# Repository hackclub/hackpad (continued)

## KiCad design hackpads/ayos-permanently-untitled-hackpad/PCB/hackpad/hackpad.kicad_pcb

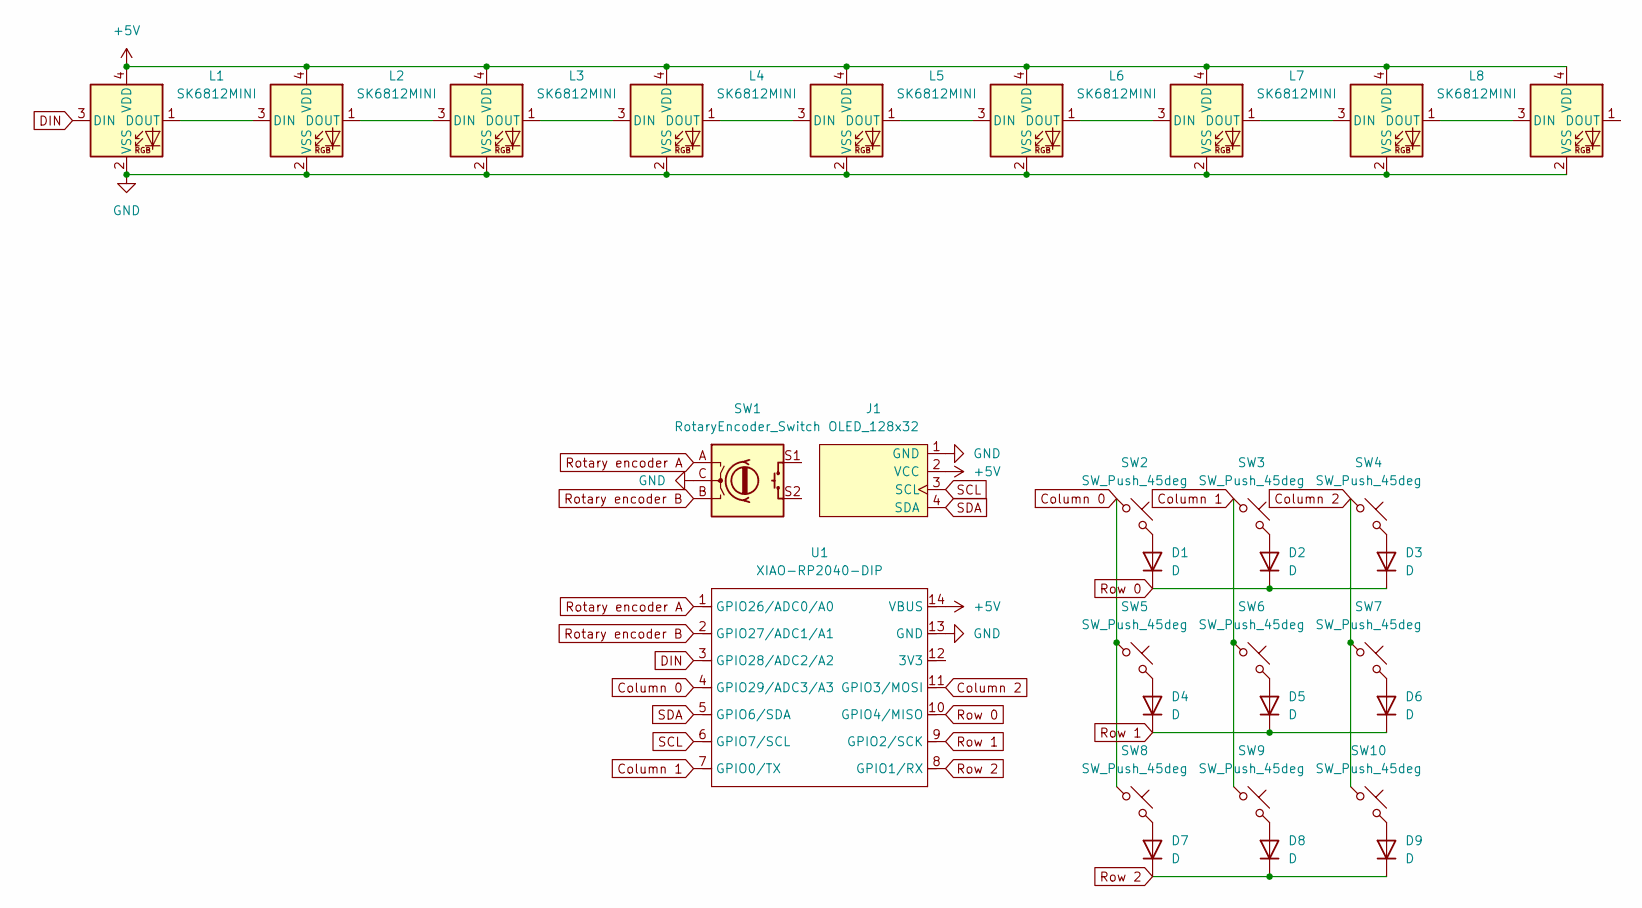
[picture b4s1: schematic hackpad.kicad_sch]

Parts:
D1, D2, D3, D4, D5, D6, D7, D8, D9: D; D_DO-35_SOD27_P7.62mm_Horizontal
J1: OLED_128x32
L1, L2, L3, L4, L5, L6, L7, L8, L9: SK6812MINI; SK6812MINI-E
SW1: RotaryEncoder_Switch; RotaryEncoder_Alps_EC11E-Switch_Vertical_H20mm_CircularMoun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
SW2, SW3, SW4, SW5, SW6, SW7, SW8, SW9, SW10: SW_Push_45deg; SW_Cherry_MX_1.00u_PCB
U1: XIAO-RP2040-DIP

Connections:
+5V: J1.2 (VCC), L1.4 (VDD), L2.4 (VDD), L3.4 (VDD), L4.4 (VDD), L5.4 (VDD), L6.4 (VDD), L7.4 (VDD), L8.4 (VDD), L9.4 (VDD), U1.14 (VBUS)
Column 0: SW2.1, SW5.1, SW8.1, U1.4 (GPIO29/ADC3/A3)
Column 1: SW3.1, SW6.1, SW9.1, U1.7 (GPIO0/TX)
Column 2: SW4.1, SW7.1, SW10.1, U1.11 (GPIO3/MOSI)
DIN: L1.3 (DIN), U1.3 (GPIO28/ADC2/A2)
GND: J1.1 (GND), L1.2 (VSS), L2.2 (VSS), L3.2 (VSS), L4.2 (VSS), L5.2 (VSS), L6.2 (VSS), L7.2 (VSS), L8.2 (VSS), L9.2 (VSS), SW1.C, U1.13 (GND)
unnamed: D1.2 (A), SW2.2
unnamed: D2.2 (A), SW3.2
unnamed: D3.2 (A), SW4.2
unnamed: D4.2 (A), SW5.2
unnamed: D5.2 (A), SW6.2
unnamed: D6.2 (A), SW7.2
unnamed: D7.2 (A), SW8.2
unnamed: D8.2 (A), SW9.2
unnamed: D9.2 (A), SW10.2
unnamed: L1.1 (DOUT), L2.3 (DIN)
unnamed: L2.1 (DOUT), L3.3 (DIN)
unnamed: L3.1 (DOUT), L4.3 (DIN)
unnamed: L4.1 (DOUT), L5.3 (DIN)
unnamed: L5.1 (DOUT), L6.3 (DIN)
unnamed: L6.1 (DOUT), L7.3 (DIN)
unnamed: L7.1 (DOUT), L8.3 (DIN)
unnamed: L8.1 (DOUT), L9.3 (DIN)
Rotary encoder A: SW1.A, U1.1 (GPIO26/ADC0/A0)
Rotary encoder B: SW1.B, U1.2 (GPIO27/ADC1/A1)
Row 0: D1.1 (K), D2.1 (K), D3.1 (K), U1.10 (GPIO4/MISO)
Row 1: D4.1 (K), D5.1 (K), D6.1 (K), U1.9 (GPIO2/SCK)
Row 2: D7.1 (K), D8.1 (K), D9.1 (K), U1.8 (GPIO1/RX)
SCL: J1.3 (SCL), U1.6 (GPIO7/SCL)
SDA: J1.4 (SDA), U1.5 (GPIO6/SDA)

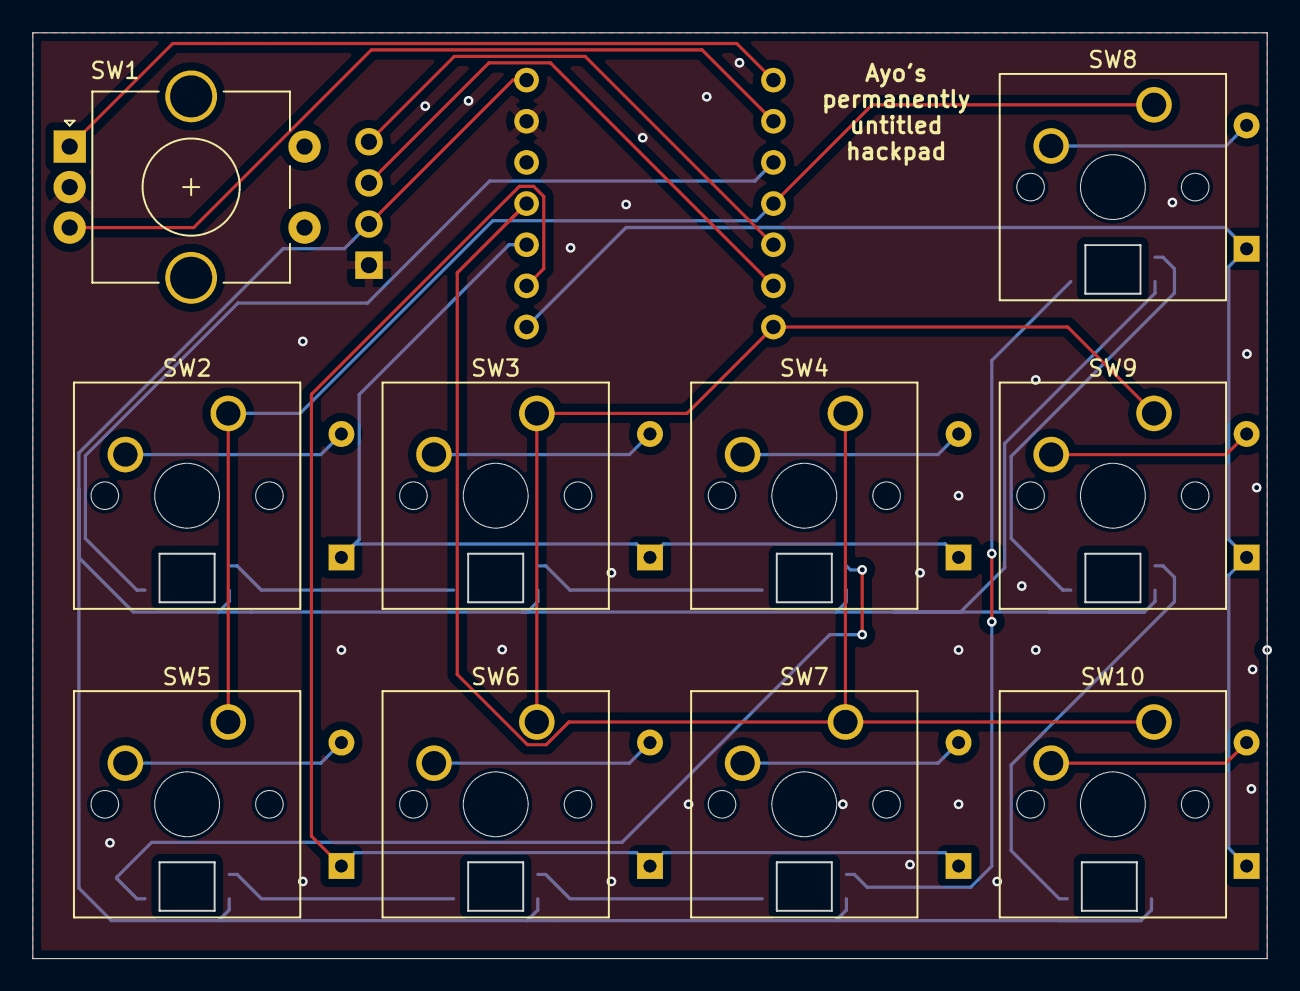
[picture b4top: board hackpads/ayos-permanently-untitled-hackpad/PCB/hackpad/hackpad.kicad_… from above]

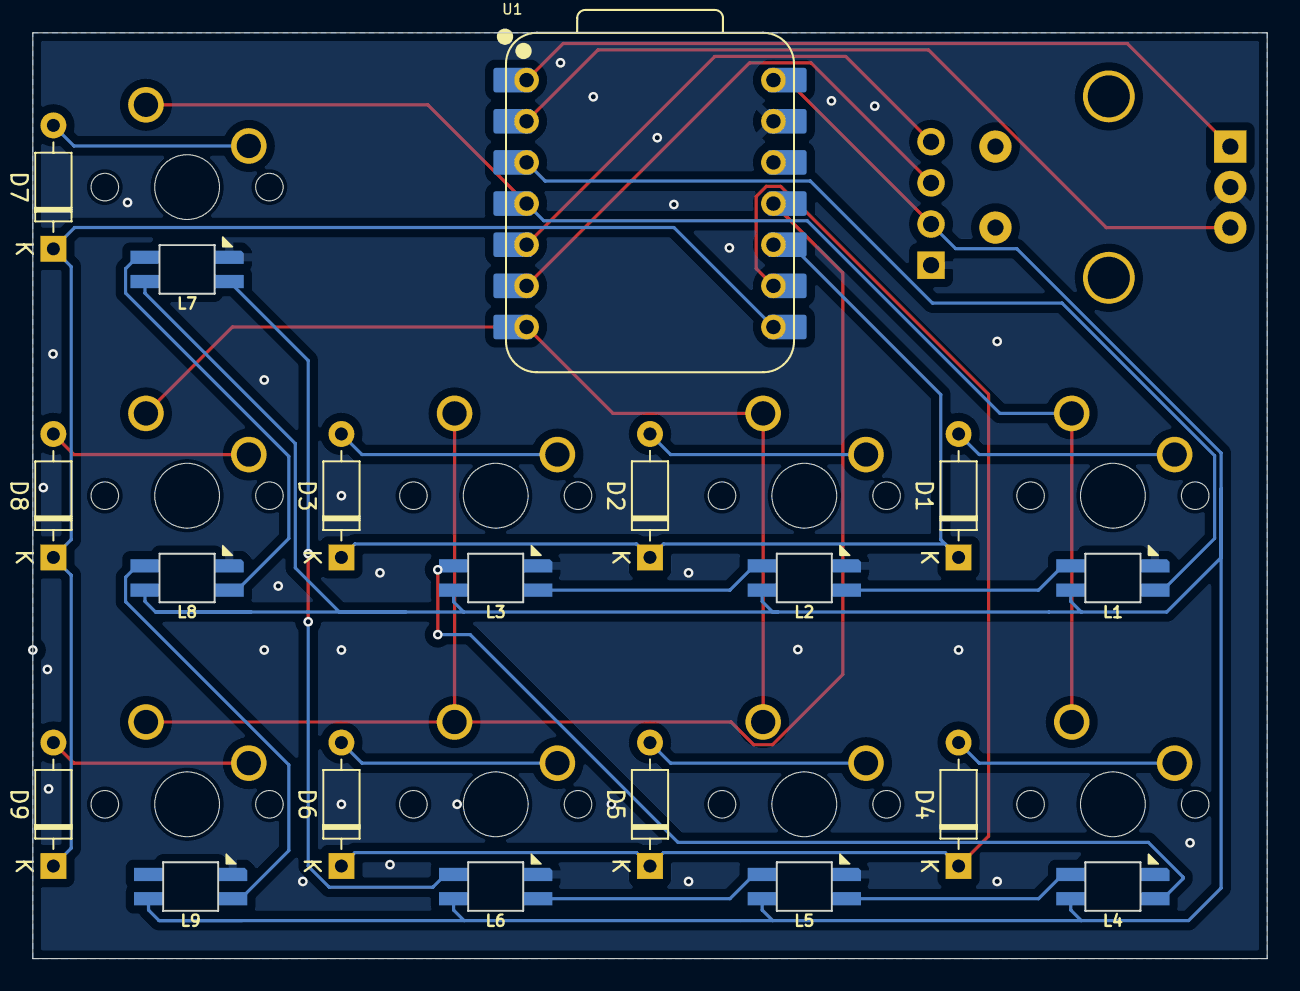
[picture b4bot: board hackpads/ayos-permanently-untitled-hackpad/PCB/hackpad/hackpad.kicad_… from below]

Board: 2 copper layers, 76.2 x 57.1 mm, 30 parts (19 on the bottom side), 30 nets.

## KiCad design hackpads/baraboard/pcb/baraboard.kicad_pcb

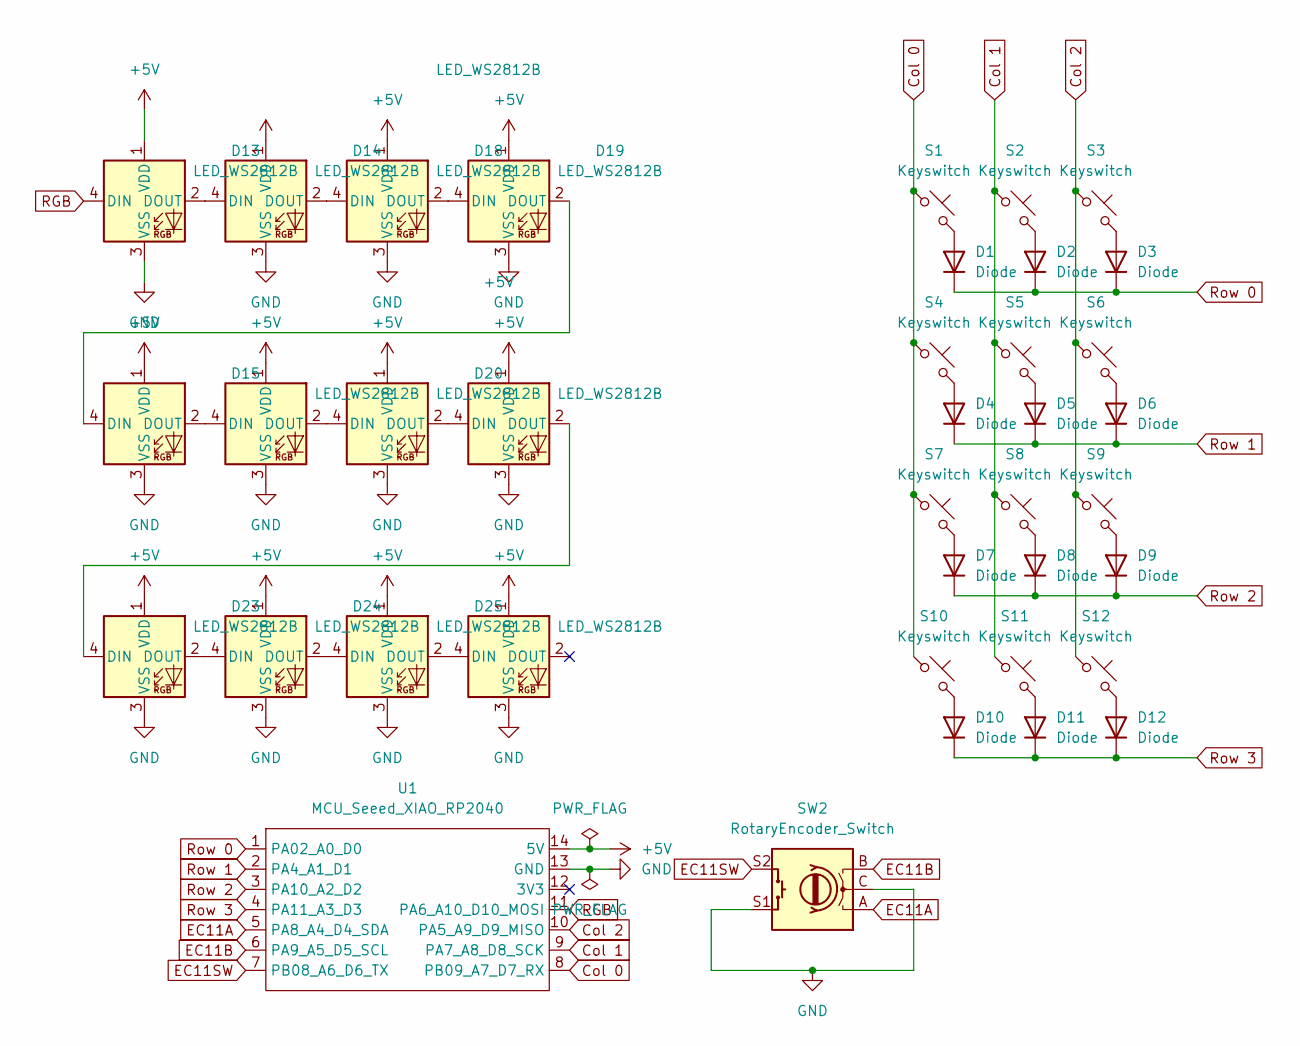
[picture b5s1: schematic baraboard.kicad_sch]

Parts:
D1, D2, D3, D4, D5, D6, D7, D8, D9, D10, D11, D12: Diode; Diode_DO-35
D13, D14, D15, D16, D18, D19, D20, D21, D23, D24, D25, D26: LED_WS2812B; LED_SK6812MINI
S1, S2, S3, S4, S5, S6, S7, S8, S9, S10, S12: Keyswitch; MX_PCB_1.00u
S11: Keyswitch; MX_PCB_2.00u
SW2: RotaryEncoder_Switch; Encoder_EC11_MX
U1: MCU_Seeed_XIAO_RP2040; Seeed_XIAO_RP2040

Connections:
+5V: D13.1 (VDD), D14.1 (VDD), D15.1 (VDD), D16.1 (VDD), D18.1 (VDD), D19.1 (VDD), D20.1 (VDD), D21.1 (VDD), D23.1 (VDD), D24.1 (VDD), D25.1 (VDD), D26.1 (VDD), U1.14 (5V)
Col 0: S1.1, S4.1, S7.1, S10.1, U1.8 (PB09_A7_D7_RX)
Col 1: S2.1, S5.1, S8.1, S11.1, U1.9 (PA7_A8_D8_SCK)
Col 2: S3.1, S6.1, S9.1, S12.1, U1.10 (PA5_A9_D9_MISO)
EC11A: SW2.A, U1.5 (PA8_A4_D4_SDA)
EC11B: SW2.B, U1.6 (PA9_A5_D5_SCL)
EC11SW: SW2.S2, U1.7 (PB08_A6_D6_TX)
GND: D13.3 (VSS), D14.3 (VSS), D15.3 (VSS), D16.3 (VSS), D18.3 (VSS), D19.3 (VSS), D20.3 (VSS), D21.3 (VSS), D23.3 (VSS), D24.3 (VSS), D25.3 (VSS), D26.3 (VSS), SW2.C, SW2.S1, U1.13 (GND)
unnamed: D1.2 (A), S1.2
unnamed: D2.2 (A), S2.2
unnamed: D3.2 (A), S3.2
unnamed: D4.2 (A), S4.2
unnamed: D5.2 (A), S5.2
unnamed: D6.2 (A), S6.2
unnamed: D7.2 (A), S7.2
unnamed: D8.2 (A), S8.2
unnamed: D9.2 (A), S9.2
unnamed: D10.2 (A), S10.2
unnamed: D11.2 (A), S11.2
unnamed: D12.2 (A), S12.2
unnamed: D13.2 (DOUT), D14.4 (DIN)
unnamed: D14.2 (DOUT), D15.4 (DIN)
unnamed: D15.2 (DOUT), D19.4 (DIN)
unnamed: D16.4 (DIN), D18.2 (DOUT)
unnamed: D16.2 (DOUT), D20.4 (DIN)
unnamed: D18.4 (DIN), D19.2 (DOUT)
unnamed: D20.2 (DOUT), D21.4 (DIN)
unnamed: D21.2 (DOUT), D23.4 (DIN)
unnamed: D23.2 (DOUT), D24.4 (DIN)
unnamed: D24.2 (DOUT), D25.4 (DIN)
unnamed: D25.2 (DOUT), D26.4 (DIN)
RGB: D13.4 (DIN), U1.11 (PA6_A10_D10_MOSI)
Row 0: D1.1 (K), D2.1 (K), D3.1 (K), U1.1 (PA02_A0_D0)
Row 1: D4.1 (K), D5.1 (K), D6.1 (K), U1.2 (PA4_A1_D1)
Row 2: D7.1 (K), D8.1 (K), D9.1 (K), U1.3 (PA10_A2_D2)
Row 3: D10.1 (K), D11.1 (K), D12.1 (K), U1.4 (PA11_A3_D3)

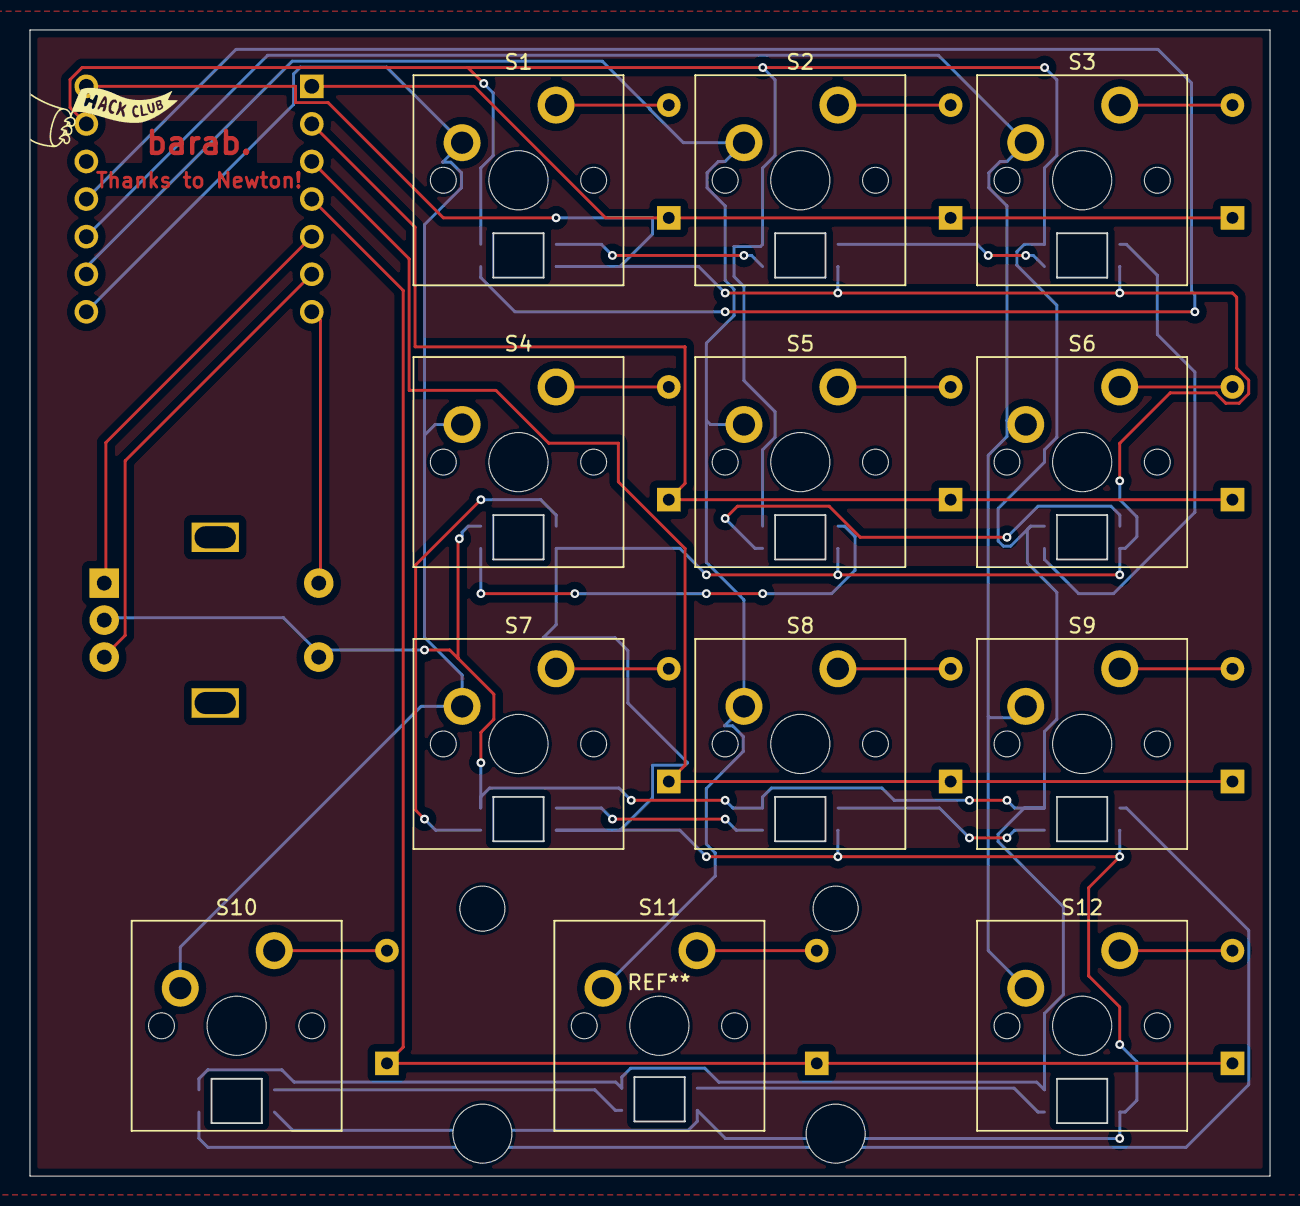
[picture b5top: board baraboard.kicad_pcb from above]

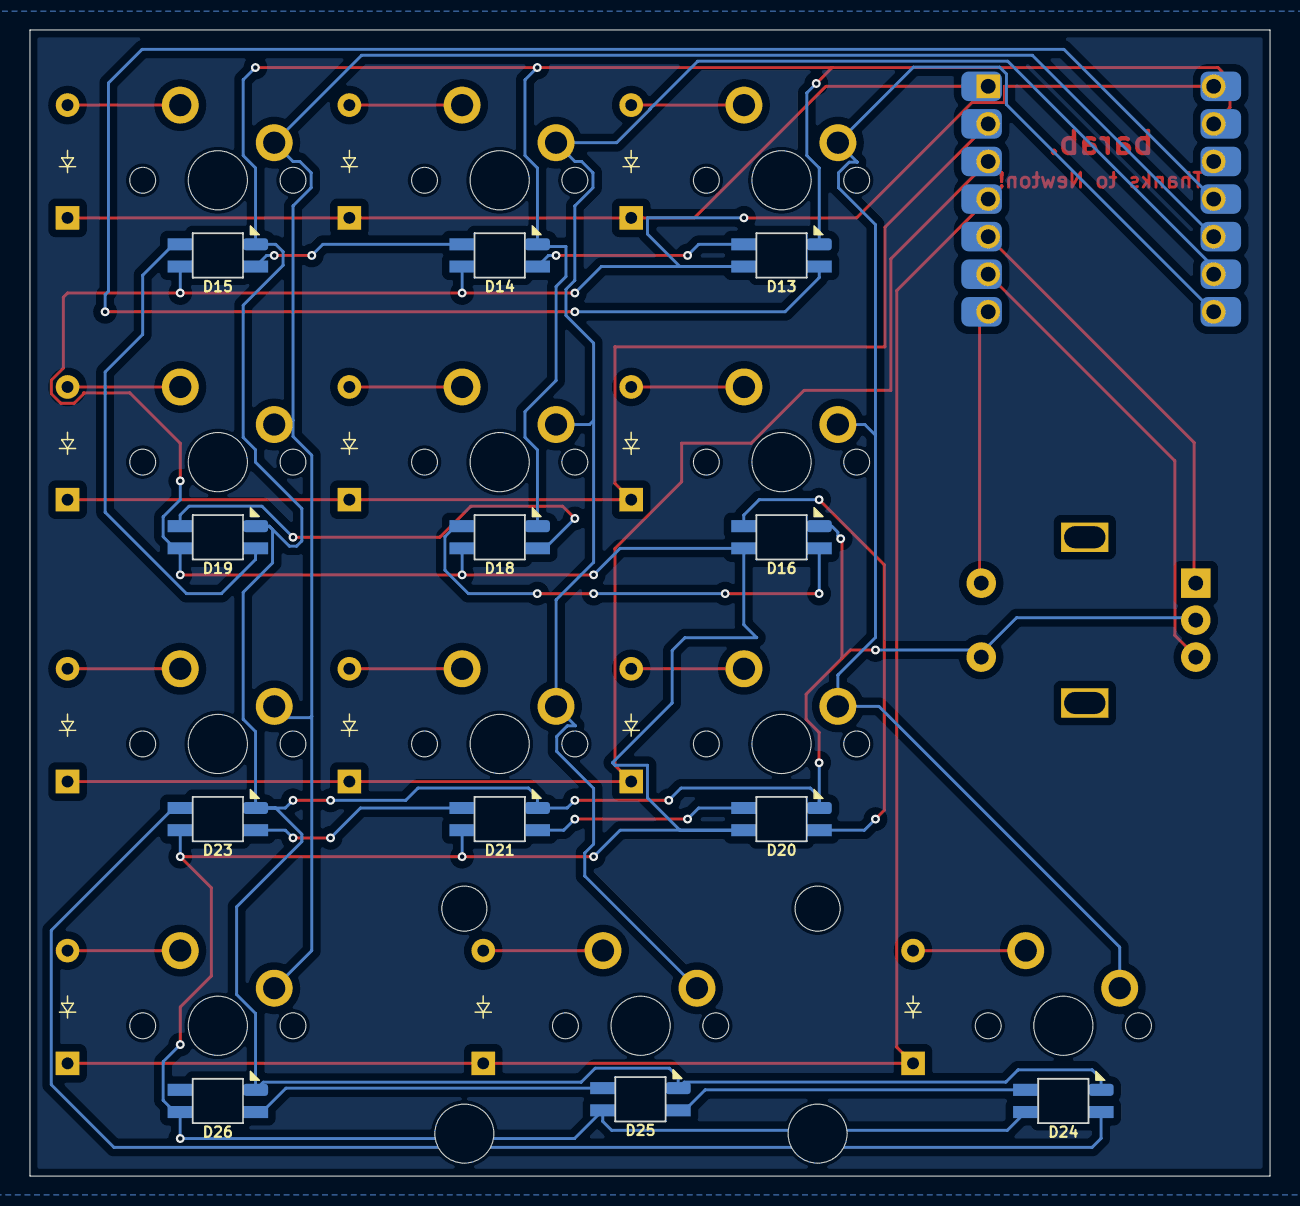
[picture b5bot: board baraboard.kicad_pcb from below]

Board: 2 copper layers, 83.8 x 77.5 mm, 38 parts (13 on the bottom side), 36 nets.

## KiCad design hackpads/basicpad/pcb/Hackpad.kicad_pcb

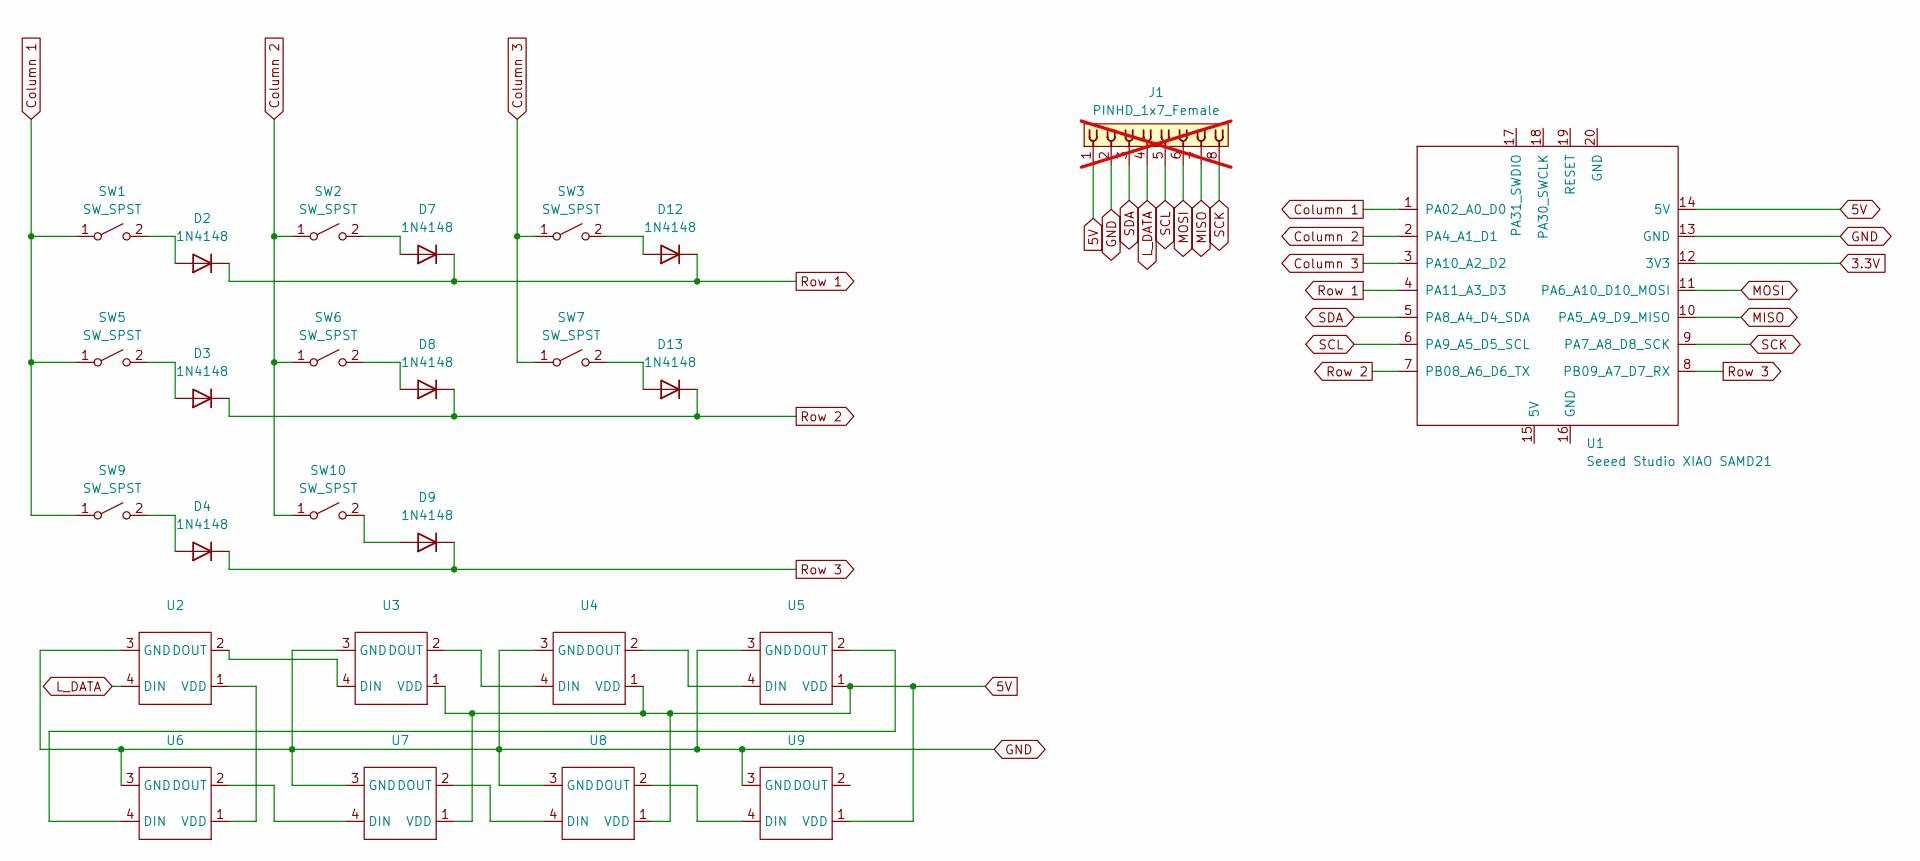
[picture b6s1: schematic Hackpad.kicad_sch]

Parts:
D2, D3, D4, D7, D8, D9, D12, D13: 1N4148; D_DO-35_SOD27_P7.62mm_Horizontal
J1: PINHD_1x7_Female; PinSocket_1x08_P2.54mm_Vertical; not fitted
SW1, SW2, SW3, SW5, SW6, SW7, SW10: SW_SPST; MX-Hotswap-1U
SW9: SW_SPST; Stabilizer_Cherry_MX_2.00u
U1: Seeed Studio XIAO SAMD21; XIAO-SAMD21-RP2040-14P-2.54-21X17.8MM (Seeeduino XIAO)
U2, U3, U4, U5, U6, U7, U8, U9: LED_SK6812MINI_PLCC4_3.5x3.5mm_P1.75mm

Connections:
3.3V: U1.12 (3V3)
5V: J1.1, U1.14 (5V), U3.1 (VDD), U4.1 (VDD), U5.1 (VDD), U7.1 (VDD), U8.1 (VDD), U9.1 (VDD)
Column 1: SW1.1 (A), SW5.1 (A), SW9.1 (A), U1.1 (PA02_A0_D0)
Column 2: SW2.1 (A), SW6.1 (A), SW10.1 (A), U1.2 (PA4_A1_D1)
Column 3: SW3.1 (A), SW7.1 (A), U1.3 (PA10_A2_D2)
GND: J1.2, U1.13 (GND), U2.3 (GND), U3.3 (GND), U4.3 (GND), U5.3 (GND), U6.3 (GND), U7.3 (GND), U8.3 (GND), U9.3 (GND)
L_DATA: J1.4, U2.4 (DIN)
MISO: J1.7, U1.10 (PA5_A9_D9_MISO)
MOSI: J1.6, U1.11 (PA6_A10_D10_MOSI)
unnamed: D2.2 (A), SW1.2 (B)
unnamed: D3.2 (A), SW5.2 (B)
unnamed: D4.2 (A), SW9.2 (B)
unnamed: D7.2 (A), SW2.2 (B)
unnamed: D8.2 (A), SW6.2 (B)
unnamed: D9.2 (A), SW10.2 (B)
unnamed: D12.2 (A), SW3.2 (B)
unnamed: D13.2 (A), SW7.2 (B)
unnamed: U2.2 (DOUT), U3.4 (DIN)
unnamed: U2.1 (VDD), U6.1 (VDD)
unnamed: U3.2 (DOUT), U4.4 (DIN)
unnamed: U4.2 (DOUT), U5.4 (DIN)
unnamed: U5.2 (DOUT), U6.4 (DIN)
unnamed: U6.2 (DOUT), U7.4 (DIN)
unnamed: U7.2 (DOUT), U8.4 (DIN)
unnamed: U8.2 (DOUT), U9.4 (DIN)
Row 1: D2.1 (K), D7.1 (K), D12.1 (K), U1.4 (PA11_A3_D3)
Row 2: D3.1 (K), D8.1 (K), D13.1 (K), U1.7 (PB08_A6_D6_TX)
Row 3: D4.1 (K), D9.1 (K), U1.8 (PB09_A7_D7_RX)
SCK: J1.8, U1.9 (PA7_A8_D8_SCK)
SCL: J1.5, U1.6 (PA9_A5_D5_SCL)
SDA: J1.3, U1.5 (PA8_A4_D4_SDA)

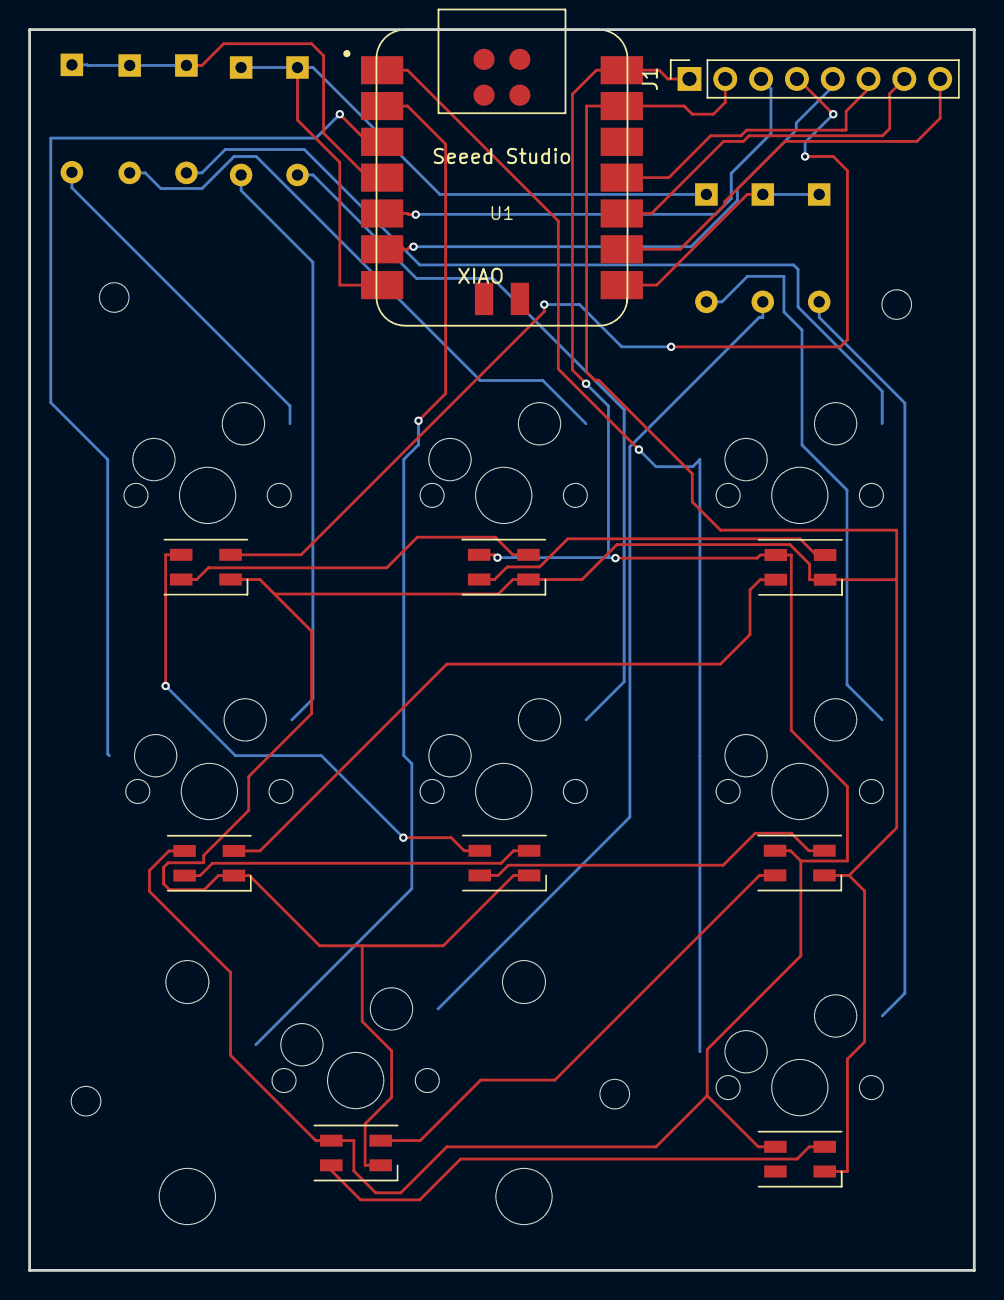
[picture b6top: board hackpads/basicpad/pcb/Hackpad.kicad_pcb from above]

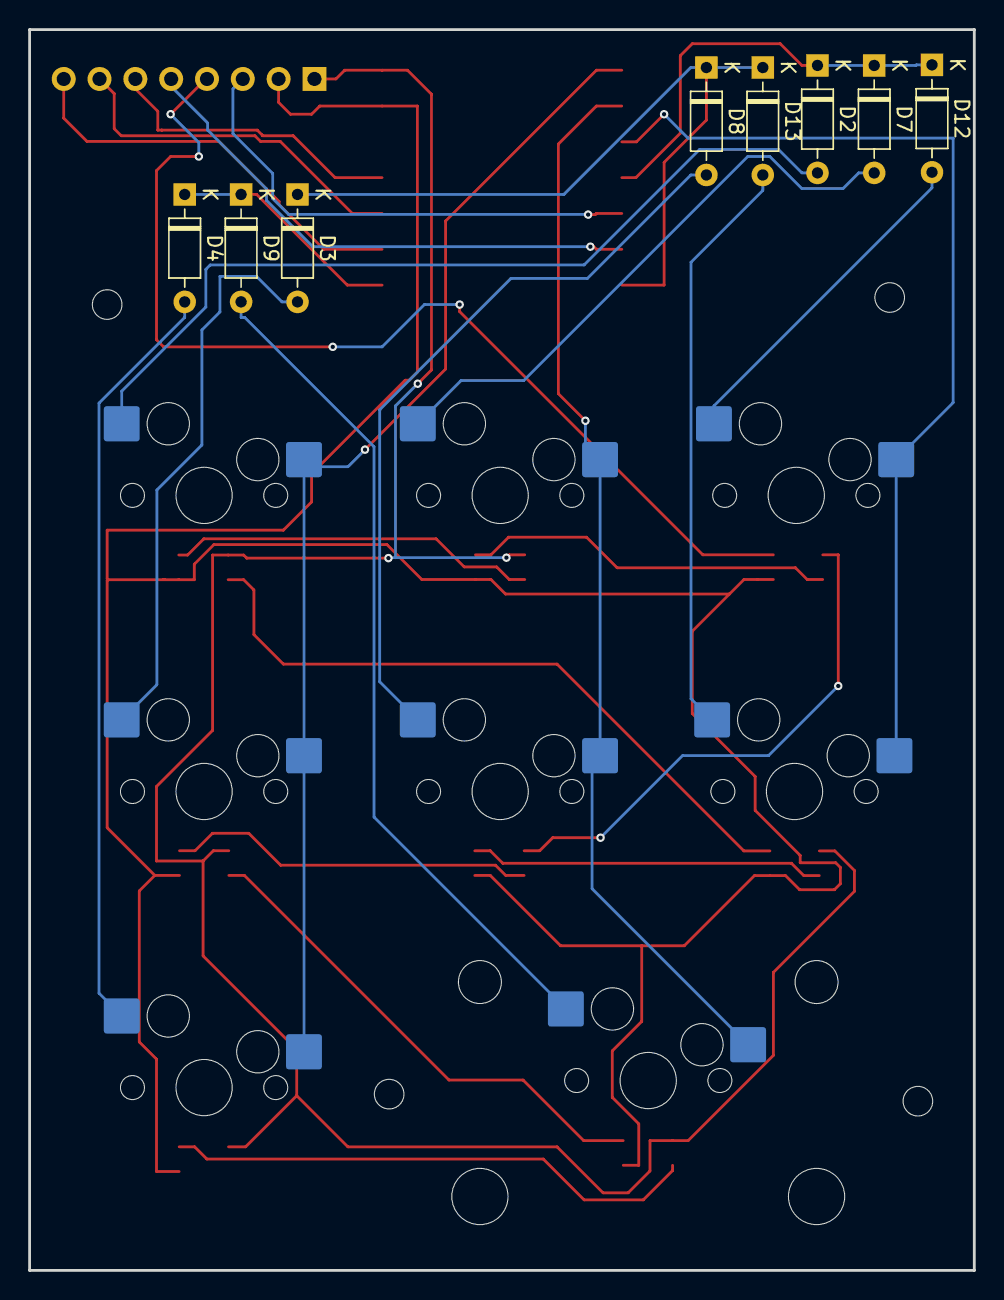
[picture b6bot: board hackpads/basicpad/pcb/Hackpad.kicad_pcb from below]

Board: 2 copper layers, 67.0 x 88.0 mm, 30 parts (16 on the bottom side), 30 nets.

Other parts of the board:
Hole1, Hole2, Hole3, Hole4: MountingHole_2.1mm

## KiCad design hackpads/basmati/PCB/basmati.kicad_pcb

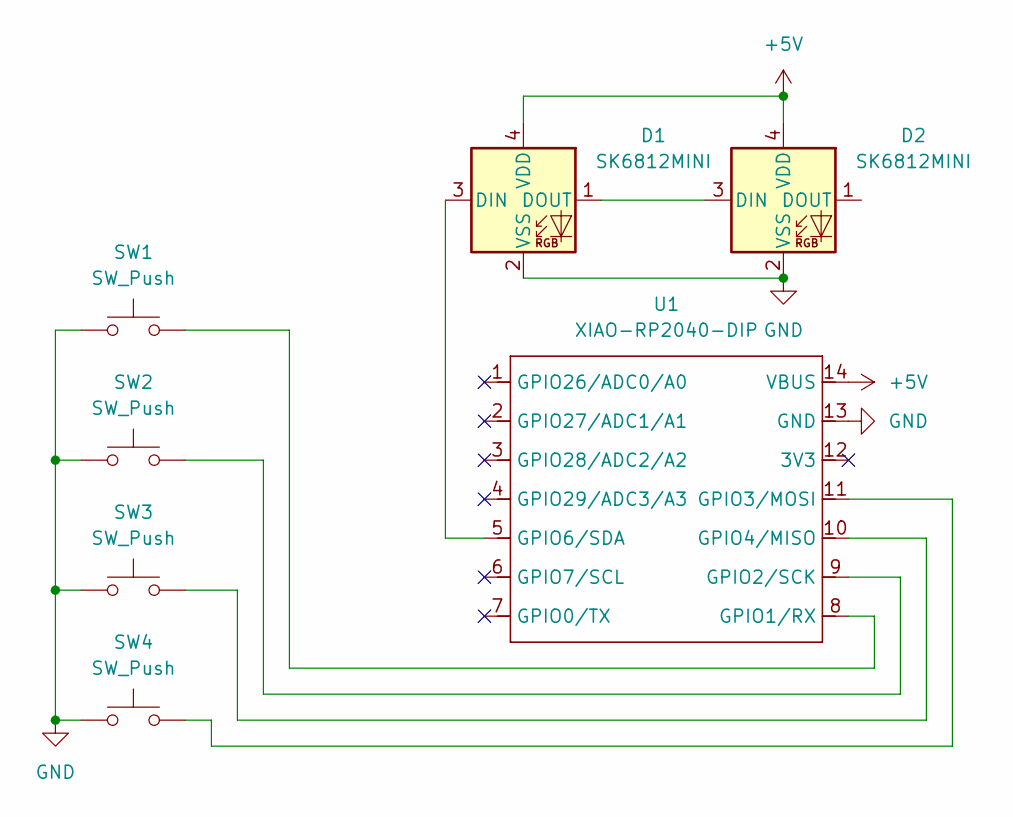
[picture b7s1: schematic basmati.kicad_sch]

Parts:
D1, D2: SK6812MINI; LED_SK6812MINI_PLCC4_3.5x3.5mm_P1.75mm
SW1, SW2, SW3, SW4: SW_Push; SW_Cherry_MX_1.00u_PCB
U1: XIAO-RP2040-DIP

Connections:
+5V: D1.4 (VDD), D2.4 (VDD), U1.14 (VBUS)
GND: D1.2 (VSS), D2.2 (VSS), SW1.1, SW2.1, SW3.1, SW4.1, U1.13 (GND)
unnamed: D1.3 (DIN), U1.5 (GPIO6/SDA)
unnamed: D1.1 (DOUT), D2.3 (DIN)
unnamed: SW1.2, U1.8 (GPIO1/RX)
unnamed: SW2.2, U1.9 (GPIO2/SCK)
unnamed: SW4.2, U1.11 (GPIO3/MOSI)
unnamed: SW3.2, U1.10 (GPIO4/MISO)

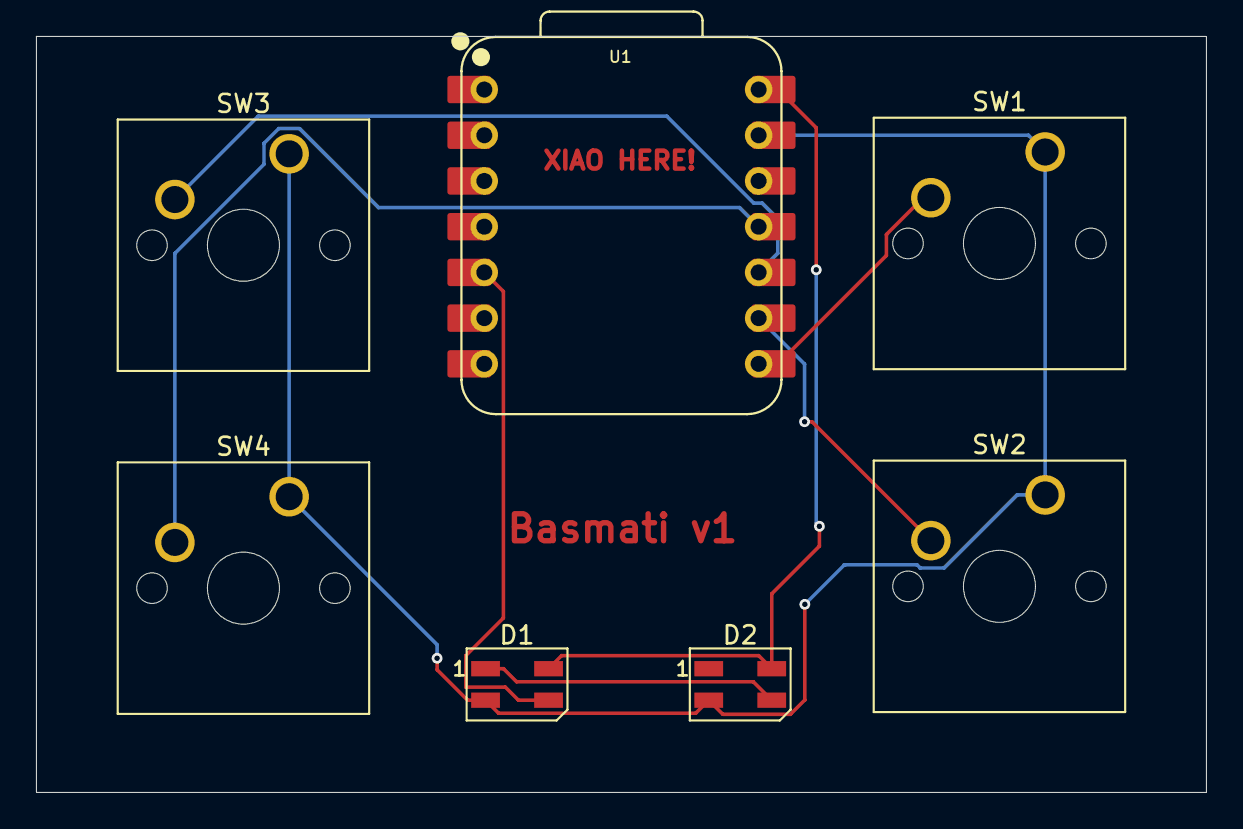
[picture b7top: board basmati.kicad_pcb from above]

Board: 2 copper layers, 65.0 x 42.0 mm, 7 parts (0 on the bottom side), 8 nets.

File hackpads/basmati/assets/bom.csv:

"Id";"Designator";"Footprint";"Quantity";"Designation";"Supplier and ref";
1;"D2,D1";"LED_SK6812MINI_PLCC4_3.5x3.5mm_P1.75mm";2;"SK6812MINI";;;
2;"U1";"XIAO-RP2040-DIP";1;"XIAO-RP2040-DIP";;;
3;"SW1,SW2,SW4,SW3";"SW_Cherry_MX_1.00u_PCB";4;"SW_Push";;;
